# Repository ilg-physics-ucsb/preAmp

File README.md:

# Speed of Sound PreAmp

This repository is intended to hold all files related tp the speed of sound preamplifier as well as instructions needed to build this device. This pre amplifier is intended for the microphones used in the speed of sound experiment, and take in a 1/4in jack and give out a BNC output with roughly 100x amplifacation factor. The preamp requires a center positive barrel jack power supply with output between 5VDC and 24VDC.

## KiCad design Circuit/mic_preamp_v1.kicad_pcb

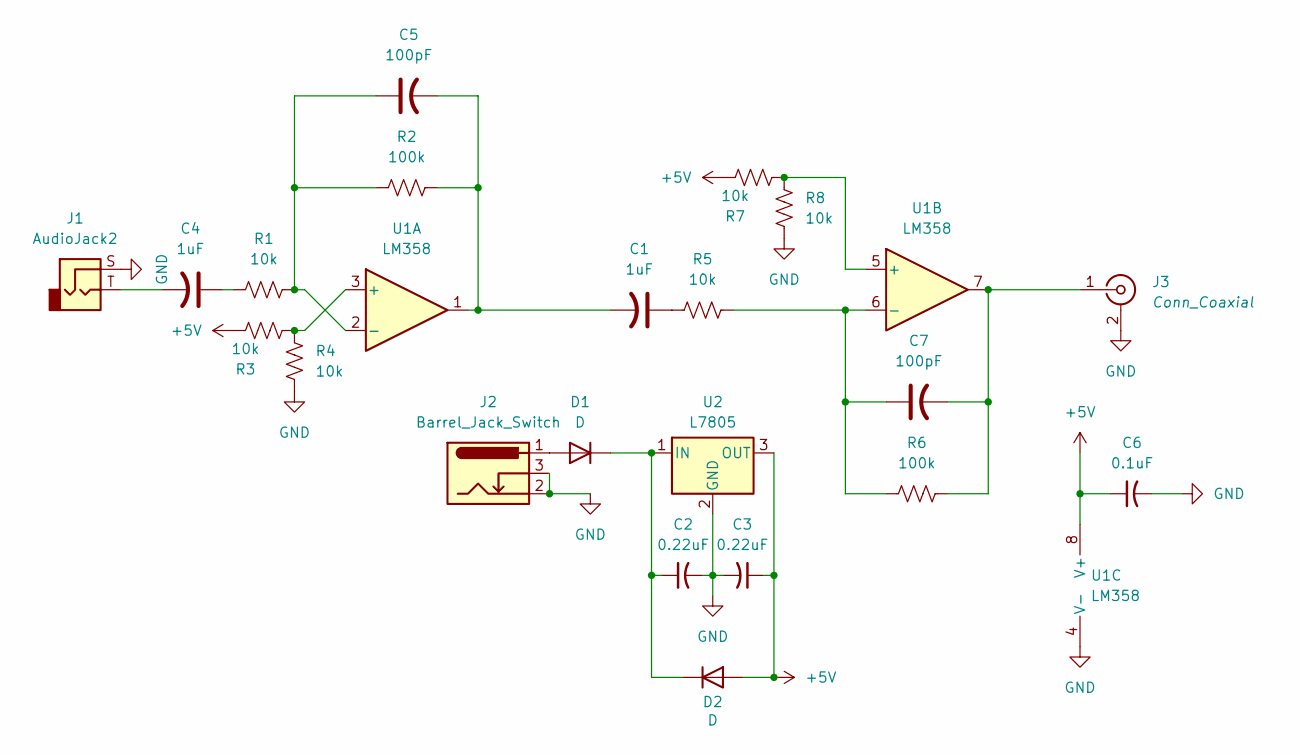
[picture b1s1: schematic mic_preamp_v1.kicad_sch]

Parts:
C1, C4: 1uF; C_Radial_D6.3mm_H5.0mm_P2.50mm
C2, C3: 0.22uF; C_Radial_D6.3mm_H5.0mm_P2.50mm
C5, C7: 100pF; C_Radial_D6.3mm_H5.0mm_P2.50mm
C6: 0.1uF; C_Radial_D6.3mm_H5.0mm_P2.50mm
D1, D2: D; D_A-405_P7.62mm_Horizontal
J1: AudioJack2; quarter inch microphone jack
J2: Barrel_Jack_Switch; BarrelJack_GCT_DCJ200-10-A_Horizontal
J3: Conn_Coaxial; BNC jack
R1, R3, R4, R5, R7, R8: 10k; R_Axial_DIN0204_L3.6mm_D1.6mm_P7.62mm_Horizontal
R2, R6: 100k; R_Axial_DIN0204_L3.6mm_D1.6mm_P7.62mm_Horizontal
U1: LM358; DIP-8_W7.62mm_LongPads
U2: L7805; TO-220F-3_Horizontal_TabDown

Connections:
+5V: C3.1, C6.1, D2.2 (A), R3.1, R7.1, U1.8 (V+), U2.3 (OUT)
GND: C2.2, C3.2, C6.2, J1.S, J2.2, J2.3, J3.2 (Ext), R4.1, R8.1, U1.4 (V-), U2.2 (GND)
unnamed: C1.1, R5.2
unnamed: C1.2, C5.2, R2.1, U1.1
unnamed: C4.1, R1.1
unnamed: C4.2, J1.T
unnamed: D1.2 (A), J2.1
unnamed: C2.1, D1.1 (K), D2.1 (K), U2.1 (IN)
unnamed: C7.2, J3.1 (In), R6.1, U1.7
unnamed: R3.2, R4.2, U1.3 (+)
unnamed: C5.1, R1.2, R2.2, U1.2 (-)
unnamed: R7.2, R8.2, U1.5 (+)
unnamed: C7.1, R5.1, R6.2, U1.6 (-)

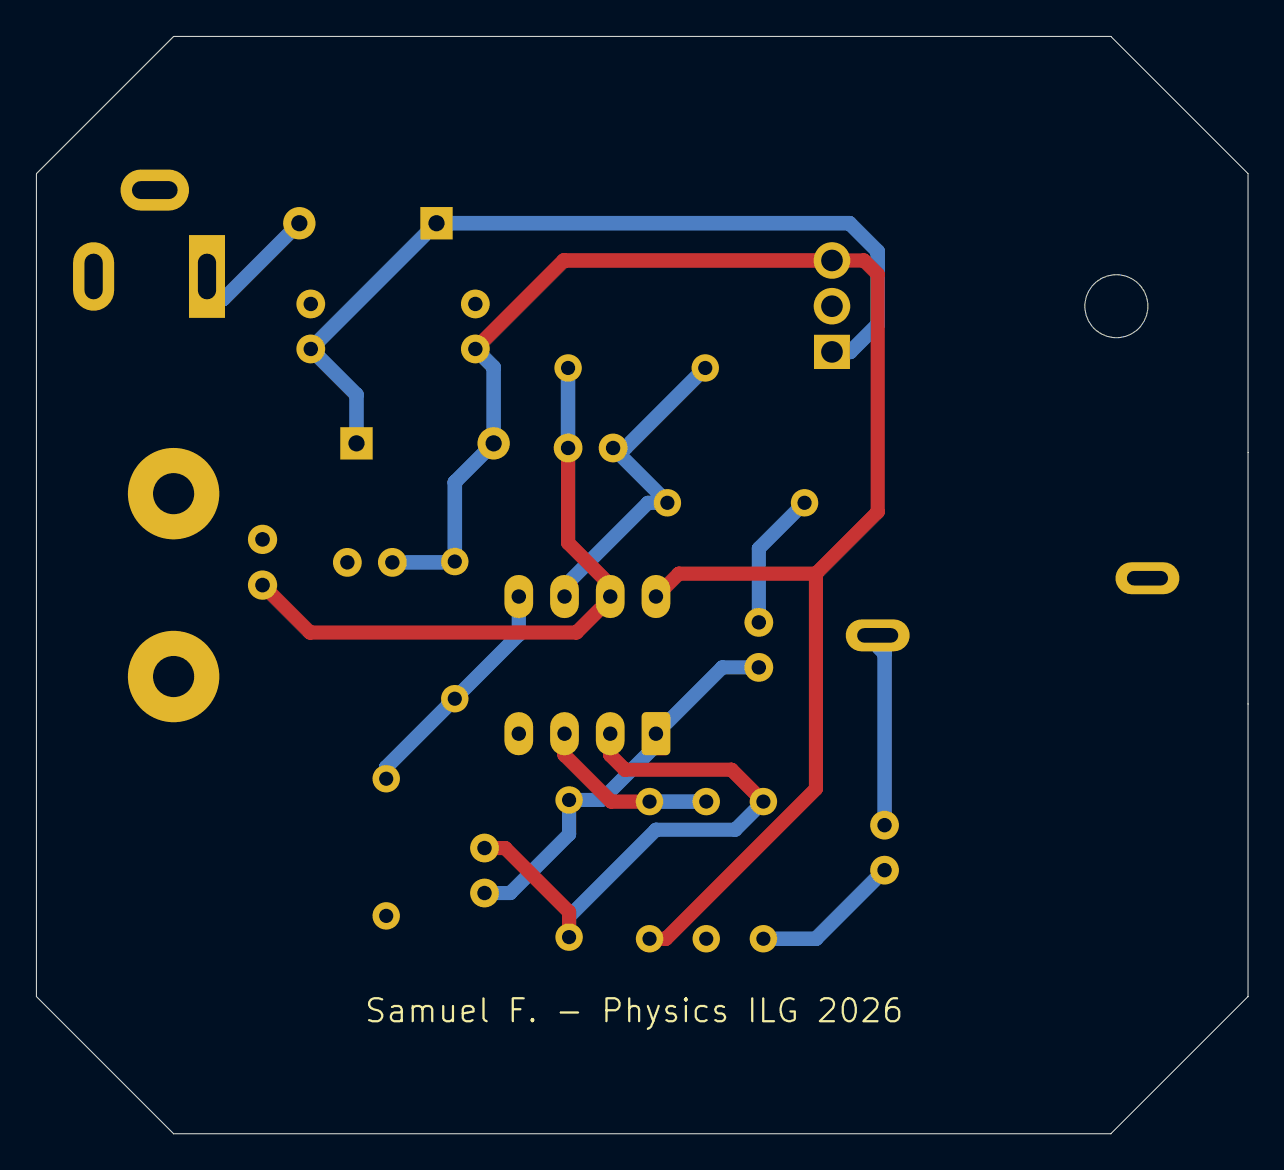
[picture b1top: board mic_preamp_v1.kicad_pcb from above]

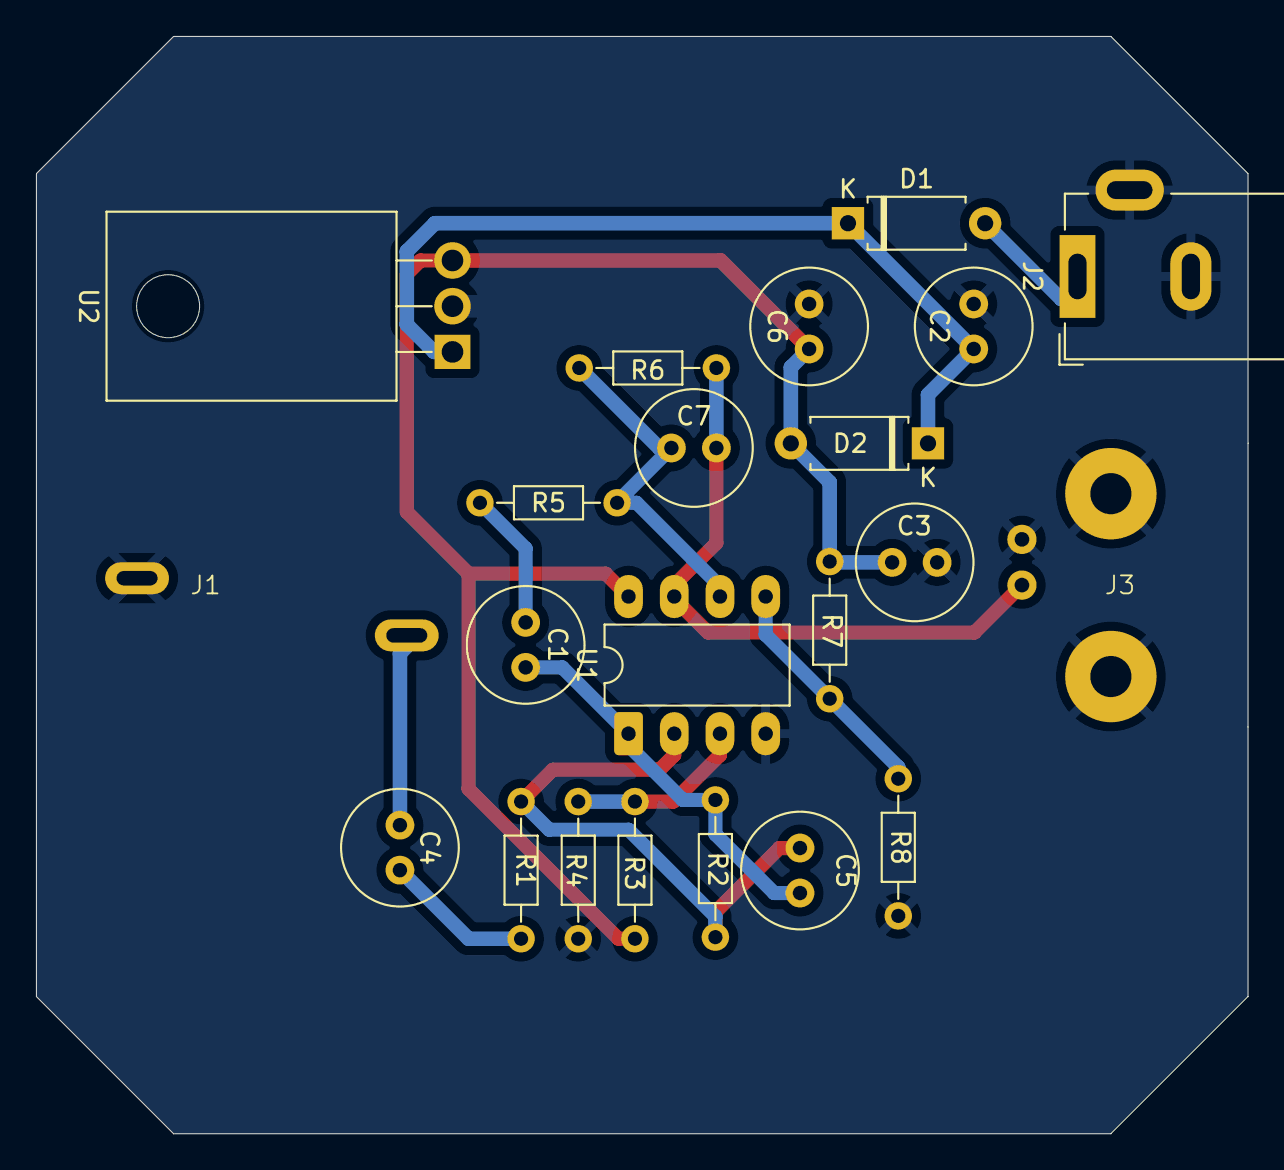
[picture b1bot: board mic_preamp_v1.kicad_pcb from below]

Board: 2 copper layers, 67.3 x 61.0 mm, 22 parts (20 on the bottom side), 13 nets.

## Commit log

2026-02-19 added circuit files
2026-02-26 Finish circuit
